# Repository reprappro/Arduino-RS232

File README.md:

# Arduino-RS232
An RS232 interface circuit for Arduinos.  

It is general-purpose, but it is primarily intended to allow an Arduino to control
a Roland Modela CNC mill (http://www.rolanddg.com/product/3d/3d/mdx-20_15/spec.html).

This allows the Modela to mill PCBs under the control of the Arduino, including the PCB
for the interface circuit itself.  So you breadboard it and get it working.  Then you mill
its PCB.  Then you take the components off your breadboard and solder them onto the PCB...

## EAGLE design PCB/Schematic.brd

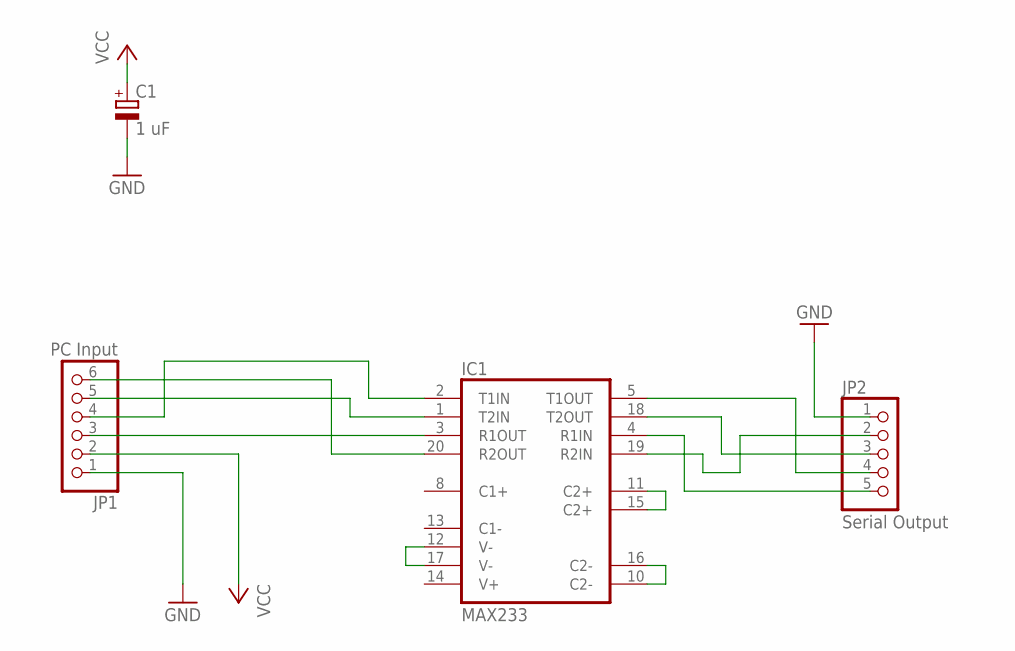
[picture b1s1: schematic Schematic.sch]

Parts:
C1: 1 uF; E2,5-6
IC1: MAX233; DIL20
JP1: PC Input; 1X06
JP2: Serial Output; 1X05

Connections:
GND: C1.-, IC1.6 (GND), IC1.9 (GND), JP1.1, JP2.1
unnamed: IC1.12 (V-), IC1.17 (V-)
unnamed: IC1.11 (C2+), IC1.15 (C2+)
unnamed: IC1.10 (C2-), IC1.16 (C2-)
unnamed: IC1.20 (R2OUT), JP1.6
unnamed: IC1.1 (T2IN), JP1.5
unnamed: IC1.2 (T1IN), JP1.4
unnamed: IC1.3 (R1OUT), JP1.3
unnamed: IC1.18 (T2OUT), JP2.3
unnamed: IC1.19 (R2IN), JP2.2
unnamed: IC1.5 (T1OUT), JP2.4
unnamed: IC1.4 (R1IN), JP2.5
VCC: C1.+, IC1.7 (VCC), JP1.2

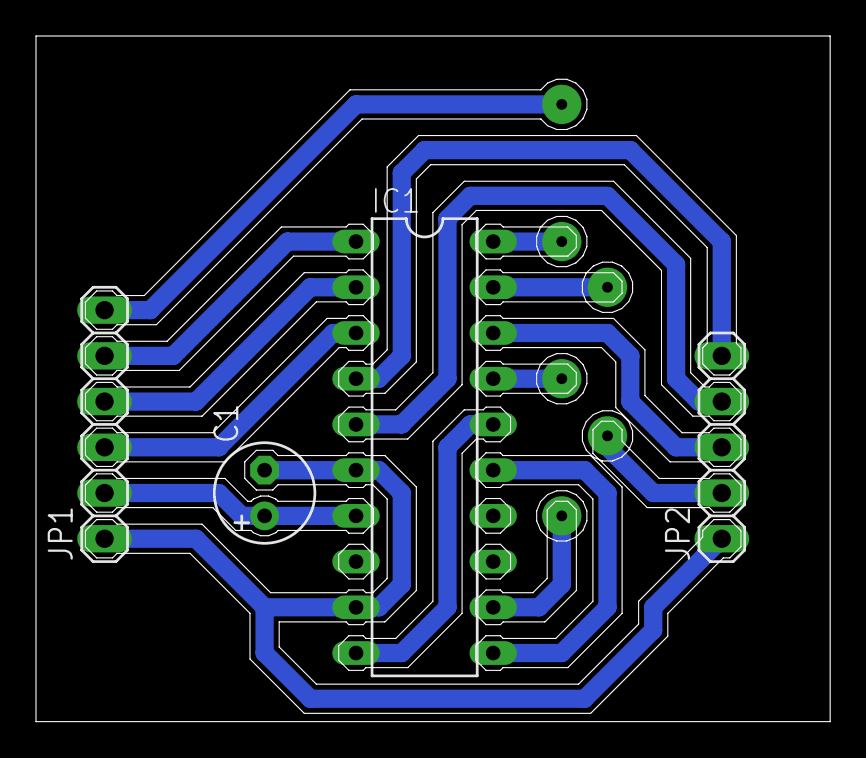
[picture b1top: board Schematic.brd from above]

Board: 2 copper layers, 44.1 x 38.1 mm, 4 parts (0 on the bottom side), 13 nets.

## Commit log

2015-07-20 README updated.
2015-07-20 All files for RS232 Driver Added
2015-07-20 STEP Files for case added
